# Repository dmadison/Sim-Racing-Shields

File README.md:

# Sim Racing Shields for Arduino

This repo contains add-on circuit boards ("shields") for connecting Arduino development boards to sim racing equipment. These shields are meant to be used in conjunction with the [Sim Racing Library for Arduino](https://github.com/dmadison/Sim-Racing-Arduino). These shields can be used to create inexpensive, standalone USB HID adapters for use with racing games and simulators.

Both of these shields are designed to be used with a [SparkFun Pro Micro, 5V (32U4)](https://github.com/sparkfun/Pro_Micro). You can use either genuine SparkFun boards or 3rd party clones. The [SparkFun Qwiic Pro Micro with a USB-C port (DEV-15795)](https://www.sparkfun.com/products/15795) is recommended. The SparkFun Pro Micro RP2040 is theoretically compatible but has not been tested. Note that the Tag-Connect programming header is not compatible with the RP2040.

The shields can be assembled with either 0.1″ female headers for prototyping or 0.1″ male headers for a permanent connection. Only assembled boards with male headers will be able to fit inside the 3D printed case.

For more information, [see the article on PartsNotIncluded.com](https://www.partsnotincluded.com/sim-racing-shields-for-arduino/).

## Logitech Shifter Shield for Pro Micro

The [Logitech Shifter Shield](pcbs/Logitech_Shifter_Shield_Pro_Micro) is designed to interface with all available Logitech shifters using a single DB-9 male connector:
* [Logitech Driving Force shifter (G923 / G920 / G29)](https://www.logitechg.com/en-us/products/driving/driving-force-shifter.html)
* [Logitech G27 shifter](https://en.wikipedia.org/wiki/Logitech_G27)
* [Logitech G25 shifter](https://en.wikipedia.org/wiki/Logitech_G25)

This repo includes firmware ([LogitechShifterShield](firmware/LogitechShifterShield/LogitechShifterShield.ino)) which works out of the box as a USB HID adapter for all three shifter types.

You can also write your own firmware using the [Sim Racing Library for Arduino](https://github.com/dmadison/Sim-Racing-Arduino). Use the `SimRacing::CreateShieldObject()` template function for easy setup with the shifter shield:

```cpp
LogitechShifterG29 shifter = SimRacing::CreateShieldObject<SimRacing::LogitechShifterG29, 2>();
LogitechShifterG27 shifter = SimRacing::CreateShieldObject<SimRacing::LogitechShifterG27, 2>();
LogitechShifterG25 shifter = SimRacing::CreateShieldObject<SimRacing::LogitechShifterG25, 2>();
```

## Logitech Pedal Shield for Pro Micro

The [Logitech Pedal Shield](pcbs/Logitech_Pedal_Shield_Pro_Micro) is designed to interface with the Logitech three pedal attachment, included with the Logitech G923 “TRUEFORCE”, G29/G920 “Driving Force”, and G27/G25 wheels, via a single DB-9 female connector.

This repo includes firmware ([LogitechPedalShield](firmware/LogitechPedalShield/LogitechPedalShield.ino)) which works out of the box as a USB HID adapter for the pedals.

You can also write your own firmware using the [Sim Racing Library for Arduino](https://github.com/dmadison/Sim-Racing-Arduino). Use the `SimRacing::CreateShieldObject()` template function for easy setup with the pedals shield:

```cpp
LogitechPedals pedals = SimRacing::CreateShieldObject<SimRacing::LogitechPedals, 2>();
```

## Firmware

The shields are designed to be used with the [Sim Racing Library for Arduino](https://github.com/dmadison/Sim-Racing-Arduino). You can use any included example for your specific hardware, or write your own using the data the library provides.

Both shields use the SparkFun Pro Micro (32U4), and firmware should be compiled using the "SparkFun Pro Micro" board in the Arduino IDE. You can find the compilation files and installation instructions for the Pro Micro [here](https://github.com/sparkfun/Arduino_Boards). You do not need to install the SparkFun boards package if you are using the custom boards package below.

### Custom Boards Installation

To install the custom boards package, start up the Arduino IDE and open the preferences window (**File > Preferences**). Copy and paste this URL for the package index into the "Additional Boards Manager URLs" field:

```
https://github.com/dmadison/Sim-Racing-Shields/raw/master/arduino-boards/boards-manager/package_simracing_index.json
```

In the menu, navigate to **Tools > Board > Boards Manager** and open up the boards manager. Search for "Sim Racing" and then install the "Sim Racing AVR Boards" package. After the package is installed you should be able to select the "SparkFun Pro Micro (for Sim Racing)" board.

### Custom Boards Configuration

The custom boards package adds two new options to the boards menu:

* USB Identity
* Serial Port

The first option, 'USB Identity', changes the USB PID and USB description for the board. Firmware compiled with the 'Shifter' option will present as "Sim Racing Shifter" with a PID of 0x9101, while firmware compiled with the 'Pedals' option will present as "Sim Racing Pedals" with a PID of 0x9102.

The second option, 'Serial Port', allows you to disable the USB CDC serial port. This improves compatibility with some systems and prevents accidentally reprogramming the board. Note that if you remove the USB CDC serial port the board will no longer automatically reset to the bootloader during programming. You will have to reset the board yourself or use an external programmer.

## Case

[A 3D printed case design](cad) is available to protect the assembled shield and microcontroller. Both shields share the same general footprint and the same case design. When assembled, the case should hold the microcontroller and shield securely without any play.

The case is printed in two parts, and assembled using two M3-10 bolts and two M3 nuts. The recommended print orientation is as-is. Note that the top half of the case is a little tricky to print, and must be printed using bed supports.

## Building Your Own

If you'd like to make these yourself, you can find the [Gerber files](https://en.wikipedia.org/wiki/Gerber_format) and [Bill of Materials (BOM)](https://en.wikipedia.org/wiki/Bill_of_materials) in [the latest release](https://github.com/dmadison/Sim-Racing-Shields/releases/latest).

## License

The files in this repository are licensed under the terms of the [GNU General Public License (GPL)](https://www.gnu.org/licenses/gpl-3.0.html), either version 3 of the License, or (at your option) any later version. See the [LICENSE](LICENSE) file for more information.

Included images are licensed under the [CC BY-NC-ND 4.0 license](https://creativecommons.org/licenses/by-nc-nd/4.0/). Attribution should be to Dave Madison ([@dmadison](https://github.com/dmadison)).

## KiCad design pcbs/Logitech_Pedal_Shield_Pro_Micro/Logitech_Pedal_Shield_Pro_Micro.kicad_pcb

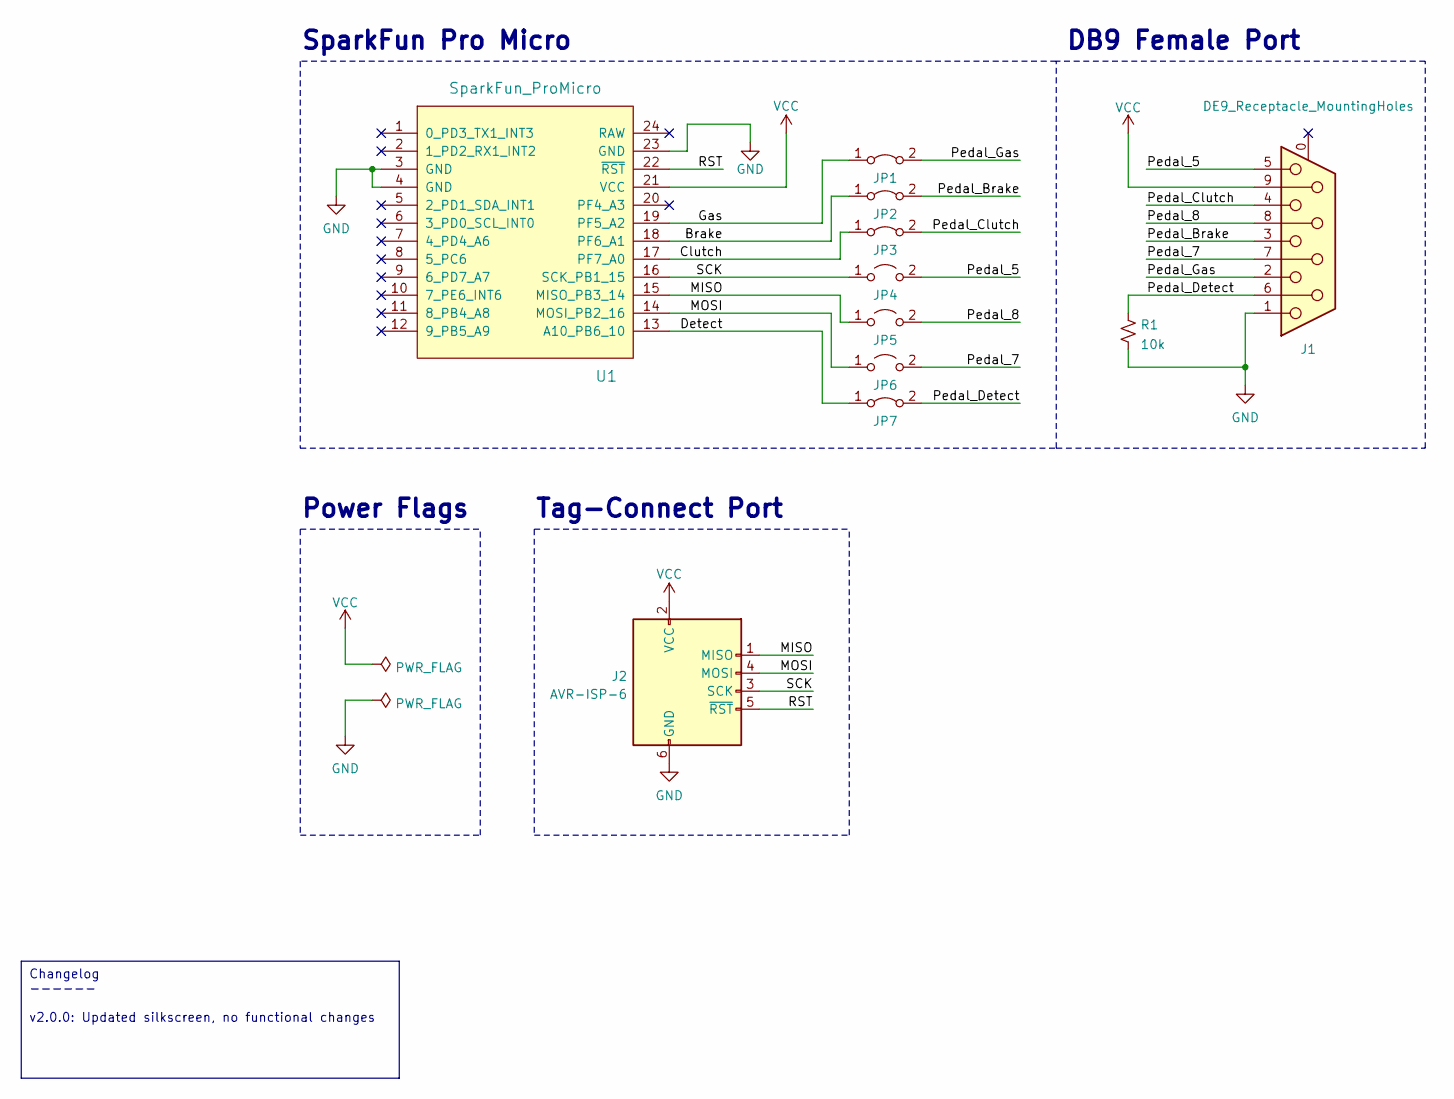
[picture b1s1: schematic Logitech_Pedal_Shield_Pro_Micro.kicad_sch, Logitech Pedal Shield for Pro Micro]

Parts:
J1: DE9_Receptacle_MountingHoles; DSUB-9_Female_Horizontal_P2.77x2.84mm_EdgePinOffset7.70mm_H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; Part Number A-DF 09 A/KG-T2S; DigiKey Part Number AE10921-ND
J2: AVR-ISP-6; Tag-Connect_TC2030-IDC-NL_2x03_P1.27mm_Vertical
JP1: Gas_Jumper; SolderJumper-2_P1.3mm_Bridged_RoundedPad1.0x1.5mm_Unmasked
JP2: Brake_Jumper; SolderJumper-2_P1.3mm_Bridged_RoundedPad1.0x1.5mm_Unmasked
JP3: Clutch_Jumper; SolderJumper-2_P1.3mm_Bridged_RoundedPad1.0x1.5mm_Unmasked
JP4, JP5, JP6: Jumper_2_Open; SolderJumper-2_P1.3mm_Open_RoundedPad1.0x1.5mm
JP7: Detect_Jumper; SolderJumper-2_P1.3mm_Bridged_RoundedPad1.0x1.5mm_Unmasked
R1: 10k; R_0805_2012Metric; Part Number RC0805FR-0710KP; DigiKey Part Number YAG1319CT-ND
U1: SparkFun_ProMicro; Sparkfun_ProMicro; Part Number DEV-15795; DigiKey Part Number 1568-DEV-15795-ND

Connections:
/Brake: JP2.1 (A), U1.18 (PF6_A1)
/Clutch: JP3.1 (A), U1.17 (PF7_A0)
/Detect: JP7.1 (A), U1.13 (A10_PB6_10)
/Gas: JP1.1 (A), U1.19 (PF5_A2)
/MISO: J2.1 (MISO), JP5.1 (A), U1.15 (MISO_PB3_14)
/MOSI: J2.4 (MOSI), JP6.1 (A), U1.14 (MOSI_PB2_16)
/Pedal_5: J1.5, JP4.2 (B)
/Pedal_7: J1.7, JP6.2 (B)
/Pedal_8: J1.8, JP5.2 (B)
/Pedal_Brake: J1.3, JP2.2 (B)
/Pedal_Clutch: J1.4, JP3.2 (B)
/Pedal_Detect: J1.6, JP7.2 (B), R1.2
/Pedal_Gas: J1.2, JP1.2 (B)
/RST: J2.5 (~RST), U1.22 (~RST)
/SCK: J2.3 (SCK), JP4.1 (A), U1.16 (SCK_PB1_15)
GND: J1.1, J2.6 (GND), R1.1, U1.3 (GND), U1.4 (GND), U1.23 (GND)
VCC: J1.9, J2.2 (VCC), U1.21 (VCC)

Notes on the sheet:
Changelog ------ v2.0.0: Updated silkscreen, no functional changes
Tag-Connect Port
Power Flags
DB9 Female Port
SparkFun Pro Micro

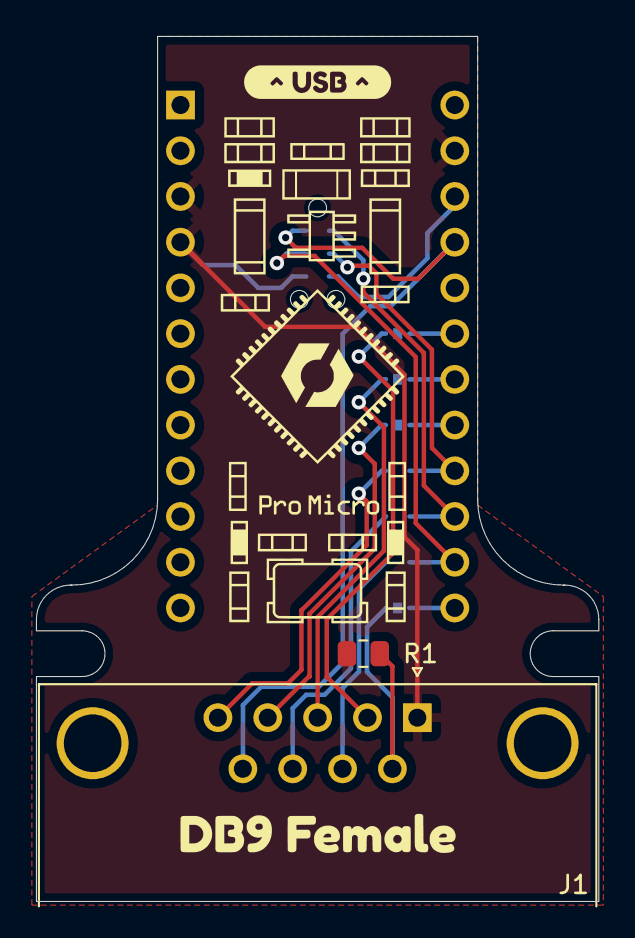
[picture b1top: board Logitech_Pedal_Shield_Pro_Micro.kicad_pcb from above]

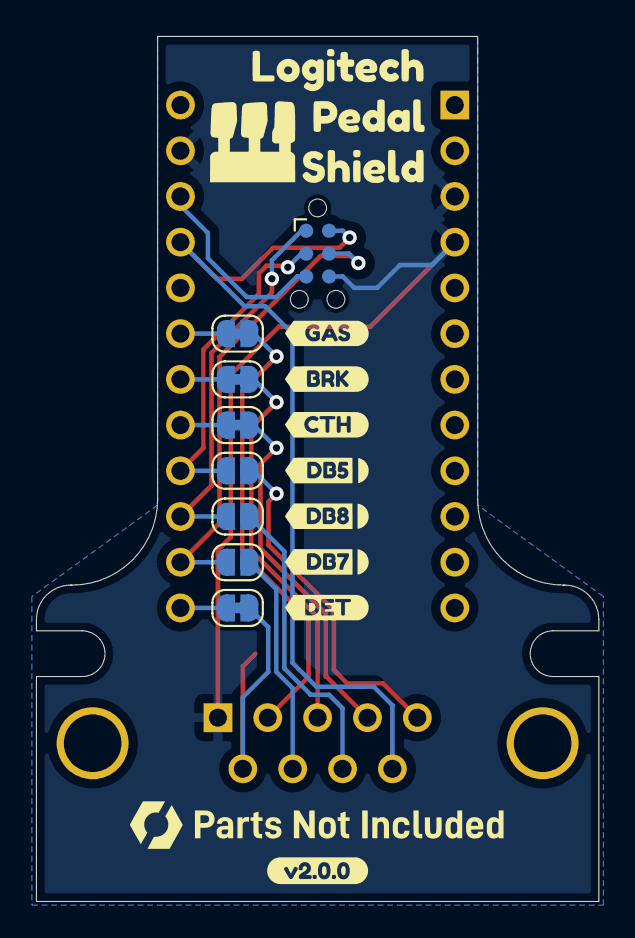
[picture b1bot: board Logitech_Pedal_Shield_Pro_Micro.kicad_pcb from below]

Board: 2 copper layers, 31.2 x 48.1 mm, 12 parts (8 on the bottom side), 17 nets.

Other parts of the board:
kibuzzard-61EDBB73: G***; kibuzzard-61EDBB73

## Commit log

2022-06-16 Created SparkFun boards files
    These are from the AVR portion of the SparkFun Arduino_Boards repo (https://github.com/sparkfun/Arduino_Boards), using the latest commit (faf2160a).
2022-06-16 Remove Unnecessary SparkFun Boards Files
    Since we're only focused on the Pro Micro, this removes all of the unnecessary files including the other bootloaders, libraries, and headers for the other variants.
2022-06-16 Remove non Pro Micro board definitions
2022-06-16 Modified Arduino boards for Sim Racing
    Using the custom USB VID/PID values from pid.codes
2022-06-17 Add boards manager package and index
    Generated using Adafruit's Arduino board package tool (BPT): https://github.com/adafruit/arduino-board-index/blob/gh-pages/bpt.py
2022-06-17 Add custom boards section to README
2022-06-20 Add 'for Arduino' to README title
    I know, *technically* you can use these outside the Arduino environment, but still.
2024-07-04 Add STLs for engraved top cases
    These are already a part of the included Fusion 360 file, but suppressed at the end of the feature tree. At the time, adding additional STLs that were identical to the existing "Top" STL in everythin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
2024-07-04 Add STLs for engraved top cases (#3)
    These are already a part of the included Fusion 360 file, but suppressed at the end of the feature tree. At the time, adding additional STLs that were identical to the existing "Top" STL in everythin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
2025-01-19 Add KiCad files to gitignore
2025-01-19 Relink DE-9 connector symbols (KiCad8)
    These symbol names' changed in the included KiCad library.
2025-01-19 Update modified schematic symbols (KiCad8)
    The power flags and AVR-ISP symbol changed in the included KiCad libraries. Updating them here to clear the ERC flags.
    This commit has no intended functional changes.
2025-01-19 Update PCBs to KiCad8 format (8.0.8)
    No intended functional changes. Open -> Save -> Close.
2025-01-19 Pedals: Fix 'wire off grid' schematic error
    Satisfies the ERC warnings.
    No intended functional change.
2025-01-19 PCBs: Set min_copper_edge_clearance
    In previous versions of KiCad this was handled by the clearance setting on the copper fill zone. Setting this to be equal to the ground pour clearance to maintain the same boundaries.
    No intended functional change.
2025-01-19 Update PCBs from schematic (KiCad8)
    Bringing in the schematic updates from the new symbols.
    No intended functional changes.
2025-01-19 KiCad 8 Format Updates (#4)
    * Add KiCad files to gitignore
    * Update PCBs to KiCad8 format (8.0.8)
    * Relink DE-9 connector symbols
    * Update modified schematic symbols
    * Pedals: Fix 'wire off grid' schematic error
    * Set min_copper_edge_clearance
2025-01-19 Add BOM to PCBs
2025-01-19 Add "Building Your Own" note to README
2025-01-19 Bill of Materials (BOM) (#5)
    Adds Bill of Materials (BOM) information to the KiCad schematic, which can be exported to CSV using the "Generate Bill of Materials" option in the toolbar of the schematic editor.
    These parts are, to the best of my knowledge, the parts I used when assembling these boards two and a half years ago. You do not need to use these exact parts, substitutes may be available that are c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
2025-01-19 PCB: Fix copper edge clearance
2025-01-23 Add v1 release dates to PCB drawing sheets
2025-01-23 Add KiCad drawing sheet template
    Includes the Parts Not Included logo and the GitHub URL for the repository
2025-01-23 Shifter: Move power to pin 9 (swap 7/9)
    This is an error on the v1 PCB, and the fundamental reason why this PCB doesn't work with the G25 shifter.
    On the Driving Force shifter, pins 7 and 9 are connected together internally in the DE-9 connector. Power applied to one goes to both pins, so one is used to power the shifter and the other is used w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
    On the G25 shifter, pins *1* and 9 are connected together internally in the DE-9 connector. Pin 7 is instead attached to the clock input of the EEPROM / shift registers, and needs to be pulsed in ord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
2025-01-23 Shifter: Changed all jumpers to NC
    We need all of these pins in order to interface with the Logitech G25 shifter
2025-03-31 Shifter: Add firmware
    Supports the Driving Force (G293 / G920 / G29), G27, and G25 shifters interchangeably.
2025-03-31 Add firmware build files to gitignore
2025-03-31 Shifter: Update bottom silkscreen files
2025-03-31 Shifter: Modify PCB for G25
2025-03-31 Shifter: Schematic to support G25
    Adds a pull-down resistor on the second 'detect' pin, and adds three series resistors to protect against shorts between the two shifter types (Driving Force / G25).
    Also renames all DE9 connections with Shift_{G25}_{G29} labels.
2025-03-31 Shifter: Add G27 notes to schematic
    Lucked out that the G25 hardware changes also support the G27.
2025-03-31 Modify README for shifter v2
2025-03-31 Pedals: Update fill zones for KiCad 8
    Using the updated fill parameters, with a small keepout zone added for the Tag Connect header
2025-03-31 Pedals: Update footprints for KiCad 8
    Changed the DE-9 and Tag-Connect footprints
2025-03-31 Pedals: Add firmware
2025-03-31 Pedals: Update PCB version to v2.0.0
    Matching the shifter, just so that the major repo version matches the PCB version to avoid confusion. No functional changes.
2025-03-31 Modify README for pedals v2
2025-03-31 Shifter: Update the date
2025-03-31 Shifter Shield Version 2 (G25 + G27) (#6)
    * Shifter: Changed all jumpers to NC
    We need all of these pins in order to interface with the Logitech G25 shifter
    * Shifter: Move power to pin 9 (swap 7/9)
    This is an error on the v1 PCB, and the fundamental reason why this PCB doesn't work with the G25 shifter.
    On the Driving Force shifter, pins 7 and 9 are connected together internally in the DE-9 connector. Power applied to one goes to both pins, so one is used to power the shifter and the other is used w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
    On the G25 shifter, pins *1* and 9 are connec
2025-03-31 Pedal Shield Version 2 (#7)
    * Pedals: Update PCB version to v2.0.0
    Matching the shifter, just so that the major repo version matches the PCB version to avoid confusion. No functional changes.
    * Pedals: Update footprints for KiCad 8
    Changed the DE-9 and Tag-Connect footprints
    * Pedals: Update fill zones for KiCad 8
    Using the updated fill parameters, with a small keepout zone added for the Tag Connect header
2025-03-31 Fix README pedals plural confusion
